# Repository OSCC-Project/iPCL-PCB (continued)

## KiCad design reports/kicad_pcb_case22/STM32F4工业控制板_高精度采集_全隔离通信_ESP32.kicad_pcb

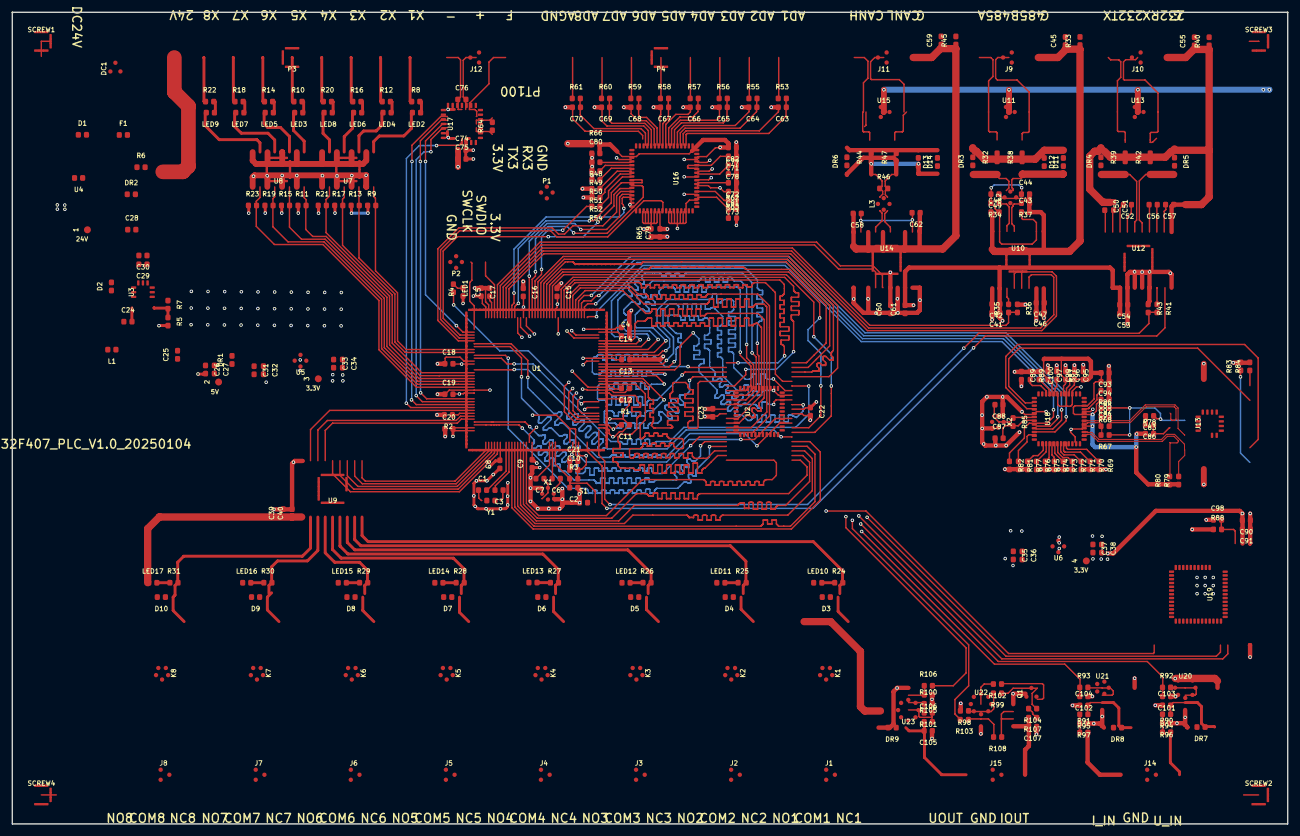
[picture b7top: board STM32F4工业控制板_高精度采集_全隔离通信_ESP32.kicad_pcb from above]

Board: 4 copper layers, 220.0 x 140.0 mm, 323 parts (0 on the bottom side), 298 nets.

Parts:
1: ie6183
2: ie6179
3: ie6175
4: ie6171
C1: ie6167
C2: ie6163
C3: ie6159
C4: ie6155
C5: ie6151
C6: ie6147
C7: ie6143
C8: ie6139
C9: ie6135
C10: ie6131
C11: ie6127
C12: ie6123
C13: ie6119
C14: ie6115
C15: ie6111
C16: ie6107
C17: ie6103
C18: ie6099
C19: ie6095
C20: ie6091
C21: ie6087
C22: ie6083
C23: ie6079
C24: ie6075
C25: ie6071
C26: ie6067
C27: ie6063
C28: ie6059
C29: ie6055
C30: ie6051
C31: ie6047
C32: ie6043
C33: ie6039
C34: ie6035
C35: ie6031
C36: ie6027
C37: ie6023
C38: ie6019
C39: ie6015
C40: ie6011
C41: ie6007
C42: ie6003
C43: ie5999
C44: ie5995
C45: ie5991
C46: ie5987
C47: ie5983
C48: ie5979
C49: ie5975
C50: ie5971
C51: ie5967
C52: ie5963
C53: ie5959
C54: ie5955
C55: ie5951
C56: ie5947
C57: ie5943
C58: ie5939
C59: ie5935
C60: ie5931
C61: ie5927
C62: ie5923
C63: ie5919
C64: ie5915
C65: ie5911
C66: ie5907
C67: ie5903
C68: ie5899
C69: ie5895
C70: ie5891
C71: ie5887
C72: ie5883
C73: ie5879
C74: ie5875
C75: ie5871
C76: ie5867
C77: ie5863
C78: ie5859
C79: ie5855
C80: ie5851
C81: ie5847
C82: ie5843
C83: ie5839
C84: ie5835
C85: ie5831
C86: ie5827
C87: ie5823
C88: ie5819
C89: ie5815
C90: ie5811
C91: ie5807
C92: ie5803
C93: ie5799
C94: ie5795
C95: ie5791
C96: ie5787
C97: ie5783
C98: ie5779
C99: ie5775
C100: ie5771
C101: ie5767
C102: ie5763
C103: ie5759
C104: ie5755
C105: ie5751
C106: ie5747
C107: ie5743
D1: ie5739
D2: ie5735
D3: ie5731
D4: ie5727
D5: ie5723
D6: ie5719
D7: ie5715
D8: ie5711
D9: ie5707
D10: ie5703
D11: ie5699
D12: ie5695
D13: ie5691
D14: ie5687
DC1: ie5683
DR1: ie5679
DR2: ie5675
DR3: ie5671
DR4: ie5667
DR5: ie5663
DR6: ie5659
DR7: ie5655
DR8: ie5651
DR9: ie5647
F1: ie5643
J1: ie5639
J2: ie5635
J3: ie5631
J4: ie5627
J5: ie5623
J6: ie5619
J7: ie5615
J8: ie5611
J9: ie5607
J10: ie5603
J11: ie5599
J12: ie5595
J13: ie4895
J14: ie5591
J15: ie5587
K1: ie5583
K2: ie5579
K3: ie5575
K4: ie5571
K5: ie5567
K6: ie5563
K7: ie5559
K8: ie5555
L1: ie5551
L2: ie5547
L3: ie5543
LED1: ie5539
LED2: ie5535
LED3: ie5531
LED4: ie5527
LED5: ie5523
LED6: ie5519
LED7: ie5515
LED8: ie5511
LED9: ie5507
LED10: ie5503
LED11: ie5499
LED12: ie5495
LED13: ie5491
LED14: ie5487
LED15: ie5483
LED16: ie5479
LED17: ie5475
P1: ie5471
P2: ie5467
P3: ie4915
P4: ie5463
Q1: ie5459
R1: ie5455
R2: ie5451
R3: ie5447
R4: ie5443
R5: ie5439
R6: ie5435
R7: ie5431
R8: ie5427
R9: ie5423
R10: ie5419
R11: ie5415
R12: ie5411
R13: ie5407
R14: ie5403
R15: ie5399
R16: ie5395
R17: ie5391
R18: ie5387
R19: ie5383
R20: ie5379
R21: ie5375
R22: ie5371
R23: ie5367
R24: ie5363
R25: ie5359
R26: ie5355
R27: ie5351
R28: ie5347
R29: ie5343
R30: ie5339
R31: ie5335
R32: ie5331
R33: ie5327
R34: ie5323
R35: ie5319
R36: ie5315
R37: ie5311
R38: ie5307
R39: ie5303
R40: ie5299
R41: ie5295
R42: ie5291
R43: ie5287
R44: ie5283
R45: ie5279
R46: ie5275
R47: ie5271
R48: ie5267
R49: ie5263
R50: ie5259
R51: ie5255
R52: ie5251
R53: ie5247
R54: ie5243
R55: ie5239
R56: ie5235
R57: ie5231
R58: ie5227
R59: ie5223
R60: ie5219
R61: ie5215
R62: ie5211
R63: ie5207
R64: ie5203
R65: ie5199
R66: ie5195
R67: ie5191
R68: ie5187
R69: ie5183
R70: ie5179
R71: ie5175
R72: ie5171
R73: ie5167
R74: ie5163
R75: ie5159
R76: ie5155
R77: ie5151
R78: ie5147
R79: ie5143
R80: ie5139
R81: ie5135
R82: ie5131
R83: ie5127
R84: ie5123
R85: ie5119
R86: ie5115
R87: ie5111
R88: ie5107
R89: ie5103
R90: ie5099
R91: ie5095
R92: ie5091
R93: ie5087
R94: ie5083
R95: ie5079
R96: ie5075
R97: ie5071
R98: ie5067
R99: ie5063
R100: ie5059
R101: ie5055
R102: ie5051
R103: ie5047
R104: ie5043
R105: ie5039
R106: ie5035
R107: ie5031
R108: ie5027
S1: ie5023
SCREW1: ie5019
SCREW2: ie5015
SCREW3: ie5011
SCREW4: ie4911
U1: ie4903
U2: ie4899
U3: ie5007
U4: ie5003
U5: ie4999
U6: ie4995
U7: ie4991
U8: ie4987
U9: ie4983
U10: ie4979
U11: ie4975
U12: ie4971
U13: ie4967
U14: ie4963
U15: ie4959
U16: ie4955
U17: ie4951
U18: ie4947
U19: ie4943
U20: ie4907
U21: ie4935
U22: ie4939
U23: ie4931
X1: ie4927
X2: ie4923
Y1: ie4919

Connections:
3.3V: 3.1, 4.1, C8.2, C9.2, C10.2, C11.2, C12.2, C13.2, C14.2, C15.2, C16.2, C17.2, C18.2, C19.2, C20.2, C21.2, C22.2, C23.2, C33.2, C34.2, C37.2, C38.2, C60.2, C74.2, C75.2, C79.2, C89.2, C90.2, C91.2, P1.1, P2.1, R3.2, R4.1, R9.1, R11.1, R13.1, R15.1, R17.1, R19.1, R21.1, R23.1, R51.2, R52.2, R63.2, R69.2, R70.2, R71.2, R77.2, R81.2, R82.2, R83.2, R84.2, R87.2, R88.1, U1.6, U1.17, U1.30, U1.32, U1.33, U1.39, U1.52, U1.62, U1.72, U1.84, U1.95, U1.108, U1.121, U1.131, U1.143, U1.144, U2.11, U2.33, U5.2, U5.4, U6.2, U6.4, U14.6, U16.23, U17.19, U17.20, U18.28, U19.2
3.3VA: C92.2, C93.2, C94.2, C95.2, C96.2, C97.2, R78.1, R79.1, R80.1, R87.1, U18.4, U18.8, U18.11, U18.15, U18.17, U18.21
5V: 2.1, C25.1, C26.2, C27.2, C31.2, C32.2, C35.2, C36.2, C41.1, C42.1, C46.2, C47.2, C53.2, C54.2, C61.2, DR1.1, L1.2, Q1.3, R5.2, R66.1, U5.3, U6.3, U10.2, U10.7, U12.2, U12.3, U14.8, U20.8, U21.8, U22.8
24V: 1.1, C28.1, C29.2, C30.2, C39.1, C40.1, D3.2, D4.2, D5.2, D6.2, D7.2, D8.2, D9.2, D10.2, DR2.1, F1.2, K1.1, K2.1, K3.1, K4.1, K5.1, K6.1, K7.1, K8.1, LED10.1, LED11.1, LED12.1, LED13.1, LED14.1, LED15.1, LED16.1, LED17.1, P3.9, R6.2, U3.7, U9.10, U23.8
232_GND: C50.1, C51.1, C55.1, C57.1, DR4.2, DR5.1, J10.1, R40.1, U12.11
232_RX: J10.2, R42.2, U13.3
232_TX: J10.3, R39.2, U13.1
485A: J9.3, R32.2, U11.1
485B: J9.2, R38.2, U11.3
485_GND: C43.2, C44.2, C45.1, C48.1, C49.1, J9.1, R33.1, R37.1, U10.9, U10.16
A5V: C80.2, C81.2, C82.2, R66.2, U16.1, U16.37, U16.38, U16.48
ACTLED: J13.10, U18.27
AD1: P4.1, R53.1
AD2: P4.2, R55.1
AD3: P4.3, R56.1
AD4: P4.4, R57.1
AD5: P4.5, R58.1
AD6: P4.6, R59.1
AD7: P4.7, R60.1
AD8: P4.8, R61.1
AD_BUSY: U1.93, U16.14
AD_CONVST: U1.98, U16.9, U16.10
AD_FASTDATA: U1.99, U16.15
AD_RANGE: R54.2, U1.91
AD_RESET: U1.92, U16.11
AD_SPI3_CS: U1.113, U16.13
AD_SPI3_MISO: U1.112, U16.24
AD_SPI3_SCLK: U1.111, U16.12
AGND: C63.2, C64.2, C65.2, C66.2, C67.2, C68.2, C69.2, C70.2, C71.1, C72.1, C73.1, C77.2, C78.1, C80.1, C81.1, C82.1, P4.9, R48.2, R49.2, R50.2, R62.2, R65.2, U16.2, U16.16, U16.17, U16.18, U16.19, U16.20, U16.21, U16.22, U16.26, U16.27, U16.28, U16.29, U16.30, U16.31, U16.32, U16.33, U16.35, U16.40, U16.41, U16.43, U16.46, U16.47, U16.50, U16.52, U16.54, U16.56, U16.58, U16.60, U16.62, U16.64
CANH: J11.3, R44.2, U15.1
CANL: J11.2, R47.2, U15.3
CAN_GND: C58.2, C59.1, C62.1, J11.1, R45.1, U14.11, U14.13, U14.16, U14.18, U14.20
COM1: J1.2, K1.2
COM2: J2.2, K2.2
COM3: J3.2, K3.2
COM4: J4.2, K4.2
COM5: J5.2, K5.2
COM6: J6.2, K6.2
COM7: J7.2, K7.2
COM8: J8.2, K8.2
DI_GND: U7.2, U7.4, U7.6, U7.8, U8.2, U8.4, U8.6, U8.8
EN: C98.2, R88.2, U19.3
ESP32_IO0: U1.45, U19.27
ESP32_RX6: U1.97, U19.37
ESP32_TX6: U1.96, U19.36
FORCE: J12.1, U17.5, U17.6
GND: C2.1, C4.2, C5.2, C8.1, C9.1, C10.1, C11.1, C12.1, C13.1, C14.1, C15.1, C16.1, C17.1, C18.1, C19.1, C20.1, C21.1, C22.1, C23.1, C25.2, C26.1, C27.1, C28.2, C29.1, C30.1, C31.1, C32.1, C33.1, C34.1, C35.1, C36.1, C37.1, C38.1, C39.2, C40.2, C41.2, C42.2, C46.1, C47.1, C53.1, C54.1, C60.1, C61.1, C74.1, C75.1, C79.1, C83.2, C86.2, C87.1, C88.1, C89.1, C90.1, C91.1, C92.1, C93.1, C94.1, C95.1, C96.1, C97.1, C98.1, C99.1, C100.1, C101.1, C102.1, C103.1, C104.1, C105.1, C106.1, C107.1, D2.1, DC1.2, DC1.3, DR1.2, DR2.2, DR7.2, DR8.2, DR9.2, J13.SH1, J13.SH2, J14.2, J15.2, P1.4, P2.4, R1.1, R2.2, R7.1, R36.1, R43.1, R65.1, R72.2, R73.2, R74.2, R75.2, R76.2, R86.1, R89.1, R96.1, R97.1, R98.2, R100.2, S1.1, U1.16, U1.31, U1.38, U1.51, U1.61, U1.83, U1.94, U1.107, U1.120, U1.130, U2.12, U2.34, U3.6, U3.9, U4.2, U5.1, U6.1, U7.9, U7.11, U7.13, U7.15, U8.9, U8.11, U8.13, U8.15, U9.9, U10.1, U10.8, U12.4, U12.5, U12.6, U12.7, U12.10, U14.1, U14.3, U14.7, U14.9, U14.10, U17.10, U17.15, U17.16, U17.21, U17.ie24, U17.ie25, U17.ie26, U17.ie27, U18.3, U18.9, U18.14, U18.16, U18.19, U18.29, U18.48, U19.1, U19.40, U19.41, U20.4, U21.4, U22.4, U23.4, X1.2, X1.4, X2.2, X2.4
I_IN2: J14.1, R91.2
I_OUT1: C107.2, J15.3, R107.2, U22.5
LINKLED: J13.11, U18.25
MCU_232_RX2: R41.2, R43.2, U1.37
MCU_232_TX2: U1.36, U12.9
MCU_485_DIR: U1.100, U10.4, U10.5
MCU_485_RX1: R35.1, R36.2, U1.102
MCU_485_TX1: U1.101, U10.6
MCU_ADC1: C101.2, R92.1, U1.42
MCU_ADC2: C102.2, R93.1, U1.43
MCU_CAN1_RX: U1.103, U14.4
MCU_CAN1_TX: U1.104, U14.5
MCU_DAC1: R103.2, U1.40
MCU_DAC2: R106.2, U1.41
MCU_DI1: R9.2, U1.116, U7.16
MCU_DI2: R13.2, U1.117, U7.14
MCU_DI3: R17.2, U1.124, U7.12
MCU_DI4: R21.2, U1.125, U7.10
MCU_DI5: R11.2, U1.126, U8.16
MCU_DI6: R15.2, U1.127, U8.14
MCU_DI7: R19.2, U1.128, U8.12
MCU_DI8: R23.2, U1.129, U8.10
MCU_OUT1: U1.1, U9.1
MCU_OUT2: U1.2, U9.2
MCU_OUT3: U1.3, U9.3
MCU_OUT4: U1.4, U9.4
MCU_OUT5: U1.5, U9.5
MCU_OUT6: U1.140, U9.6
MCU_OUT7: U1.139, U9.7
MCU_OUT8: U1.137, U9.8
NC1: J1.3, K1.4
NC2: J2.3, K2.4
NC3: J3.3, K3.4
NC4: J4.3, K4.4
NC5: J5.3, K5.4
NC6: J6.3, K6.4
NC7: J7.3, K7.4
NC8: J8.3, K8.4
NETC1_1: C1.1, Y1.2
NETC3_1: C3.1, Y1.1
NETC4_1: C4.1, U1.71
NETC5_1: C5.1, U1.106
NETC6_1: C6.1, X1.3
NETC7_1: C7.1, X1.1
NETC24_1: C24.1, D2.2, L1.1, U3.8
NETC24_2: C24.2, U3.1
NETC43_1: C43.1, C44.1, C48.2, C49.2, R34.2, U10.10, U10.15
NETC50_2: C50.2, U12.20
NETC51_2: C51.2, U12.19
NETC52_1: C52.1, U12.17
NETC52_2: C52.2, U12.18
NETC56_1: C56.1, U12.13
NETC56_2: C56.2, U12.14
NETC57_2: C57.2, U12.12
NETC58_1: C58.1, C62.2, U14.12, U14.19
NETC71_2: C71.2, U16.44, U16.45
NETC72_2: C72.2, U16.39
NETC73_2: C73.2, U16.36
NETC84_2: C84.2, J13.6
NETC85_2: C85.2, J13.3
NETC87_2: C87.2, R85.2, U18.31, X2.3
NETC88_2: C88.2, R85.1, U18.30, X2.1
NETC99_2: C99.2, U18.20
NETC100_2: C100.2, U18.22
NETC103_2: C103.2, DR7.1, R94.1, U20.3
NETC104_2: C104.2, DR8.1, R95.1, U21.3
NETC106_2: C106.2, R106.1, U23.3
NETD1_1: D1.1, DC1.1
NETD1_2: D1.2, F1.1
NETD11_1: D11.1, D12.2, DR3.2
NETD11_2: D11.2, D12.1, L2.3, R38.1
NETD13_1: D13.1, D14.2, L3.4, R44.1, R46.1
NETD13_2: D13.2, D14.1, DR6.2
NETDR3_1: DR3.1, L2.4, R32.1
NETDR4_1: DR4.1, R39.1, U12.16
NETDR5_2: DR5.2, R42.1, U12.15
NETDR6_1: DR6.1, L3.3, R46.2, R47.1
NETJ13_9: J13.9, R83.1
NETJ13_12: J13.12, R84.1
NETL2_1: L2.1, R34.1, U10.14
NETL2_2: L2.2, R37.2, U10.13
NETL3_1: L3.1, U14.17
NETL3_2: L3.2, U14.15
NETLED1_1: LED1.1, R4.2
NETLED2_1: LED2.1, R8.2
NETLED2_2: LED2.2, U7.1
NETLED3_1: LED3.1, R10.2
NETLED3_2: LED3.2, U8.1
NETLED4_1: LED4.1, R12.2
NETLED4_2: LED4.2, U7.3
NETLED5_1: LED5.1, R14.2
NETLED5_2: LED5.2, U8.3
NETLED6_1: LED6.1, R16.2
NETLED6_2: LED6.2, U7.5
NETLED7_1: LED7.1, R18.2
NETLED7_2: LED7.2, U8.5
NETLED8_1: LED8.1, R20.2
NETLED8_2: LED8.2, U7.7
NETLED9_1: LED9.1, R22.2
NETLED9_2: LED9.2, U8.7
NETLED10_2: LED10.2, R24.1
NETLED11_2: LED11.2, R25.1
NETLED12_2: LED12.2, R26.1
NETLED13_2: LED13.2, R27.1
NETLED14_2: LED14.2, R28.1
NETLED15_2: LED15.2, R29.1
NETLED16_2: LED16.2, R30.1
NETLED17_2: LED17.2, R31.1
NETQ1_1: Q1.1, R102.1
NETQ1_2: Q1.2, R99.1, R104.1
NETR1_2: R1.2, U1.48
NETR2_1: R2.1, U1.138
NETR5_1: R5.1, R7.2, U3.4
NETR6_1: R6.1, U4.1
NETR35_2: R35.2, U10.3
NETR41_1: R41.1, U12.8
NETR48_1: R48.1, U16.3
NETR49_1: R49.1, U16.4
NETR50_1: R50.1, U16.5
NETR51_1: R51.1, U16.6
NETR52_1: R52.1, U16.7
NETR54_1: R54.1, U16.8
NETR62_1: R62.1, R63.1, U16.34
NETR64_1: R64.1, U17.1, U17.2
NETR64_2: R64.2, U17.3, U17.4
NETR69_1: R69.1, U18.45
NETR70_1: R70.1, U18.44
NETR71_1: R71.1, U18.43
NETR72_1: R72.1, U18.42
NETR73_1: R73.1, U18.41
NETR74_1: R74.1, U18.40
NETR75_1: R75.1, U18.39
NETR76_1: R76.1, U18.38
NETR77_1: R77.1, U18.37
NETR81_1: R81.1, U18.36
NETR86_2: R86.2, U18.10
NETR89_2: R89.2, U18.23
NETR90_1: R90.1, R94.2, R96.2
NETR91_1: R91.1, R95.2, R97.2
NETR92_2: R92.2, U20.1, U20.2
NETR93_2: R93.2, U21.1, U21.2
NETR98_1: R98.1, R99.2, U22.2
NETR100_1: R100.1, R101.2, U23.2
NETR101_1: R101.1, R105.2, U23.1
NETR102_2: R102.2, U22.1
NETR103_1: R103.1, R108.2, U22.3
NETR104_2: R104.2, R107.1
NETR108_1: R108.1, U22.6, U22.7
NO1: J1.1, K1.3
NO2: J2.1, K2.3
NO3: J3.1, K3.3
NO4: J4.1, K4.3
NO5: J5.1, K5.3
NO6: J6.1, K6.3
NO7: J7.1, K7.3
NO8: J8.1, K8.3
NRST: C2.2, R3.1, S1.2, U1.25
OSC32_IN: C1.2, U1.8
OSC32_OUT: C3.2, U1.9
OSC_IN: C7.2, U1.23
OSC_OUT: C6.2, U1.24
OUT1: D3.1, K1.5, R24.2, U9.18
OUT2: D4.1, K2.5, R25.2, U9.17
OUT3: D5.1, K3.5, R26.2, U9.16
OUT4: D6.1, K4.5, R27.2, U9.15
OUT5: D7.1, K5.5, R28.2, U9.14
OUT6: D8.1, K6.5, R29.2, U9.13
OUT7: D9.1, K7.5, R30.2, U9.12
OUT8: D10.1, K8.5, R31.2, U9.11
PGND: C45.2, C55.2, C59.2, R33.2, R40.2, R45.2, SCREW1.1, SCREW2.1, SCREW3.1, SCREW4.1, U11.2, U13.2, U15.2
PT_DRDY: U1.136, U17.18
PT_SPI1_CS: U1.110, U17.13
PT_SPI1_MISO: U1.134, U17.14
PT_SPI1_MOSI: U1.135, U17.11
PT_SPI1_SCLK: U1.133, U17.12
RCT: C83.1, J13.5, R67.1, R68.1
RTD+: C76.2, J12.2, U17.7
RTD-: C76.1, J12.3, U17.8, U17.9
RUN: LED1.2, U1.47
RX3: P1.3, U1.70
RXN: C84.1, R67.2, U18.5
RXP: C85.1, R68.2, U18.6
SRAM_A0: U1.10, U2.5
SRAM_A1: U1.11, U2.4
SRAM_A2: U1.12, U2.3
SRAM_A3: U1.13, U2.2
SRAM_A4: U1.14, U2.1
SRAM_A5: U1.15, U2.44
SRAM_A6: U1.50, U2.43
SRAM_A7: U1.53, U2.42
SRAM_A8: U1.54, U2.27
SRAM_A9: U1.55, U2.26
SRAM_A10: U1.56, U2.25
SRAM_A11: U1.57, U2.24
SRAM_A12: U1.87, U2.22
SRAM_A13: U1.88, U2.21
SRAM_A14: U1.89, U2.20
SRAM_A15: U1.90, U2.19
SRAM_A16: U1.80, U2.18
SRAM_A17: U1.81, U2.23
SRAM_A18: U1.82, U2.28
SRAM_CS1: U1.123, U2.6
SRAM_D0: U1.85, U2.7
SRAM_D1: U1.86, U2.8
SRAM_D2: U1.114, U2.9
SRAM_D3: U1.115, U2.10
SRAM_D4: U1.58, U2.13
SRAM_D5: U1.59, U2.14
SRAM_D6: U1.60, U2.15
SRAM_D7: U1.63, U2.16
SRAM_D8: U1.64, U2.29
SRAM_D9: U1.65, U2.30
SRAM_D10: U1.66, U2.31
SRAM_D11: U1.67, U2.32
SRAM_D12: U1.68, U2.35
SRAM_D13: U1.77, U2.36
SRAM_D14: U1.78, U2.37
SRAM_D15: U1.79, U2.38
SRAM_LB: U1.141, U2.39
SRAM_OE: U1.118, U2.41
SRAM_UB: U1.142, U2.40
SRAM_WE: U1.119, U2.17
SWCLK: P2.3, U1.109
SWDIO: P2.2, U1.105
TCT: C86.1, J13.4, R78.2
TX3: P1.2, U1.69
TXN: J13.2, R80.2, U18.1
TXP: J13.1, R79.2, U18.2
U_IN1: J14.3, R90.2
U_OUT2: C105.2, DR9.1, J15.1, R105.1
V1: C63.1, R53.2, U16.49
V2: C64.1, R55.2, U16.51
V3: C65.1, R56.2, U16.53
V4: C66.1, R57.2, U16.55
V5: C67.1, R58.2, U16.57
V6: C68.1, R59.2, U16.59
V7: C69.1, R60.2, U16.61
V8: C70.1, R61.2, U16.63
VREF2.5V: C77.1, C78.2, U16.42
W5500_SPI2_CS: R82.1, U1.73, U18.32
W5500_SPI2_MISO: U1.75, U18.34
W5500_SPI2_MOSI: U1.76, U18.35
W5500_SPI2_SCLK: U1.74, U18.33
X1: P3.1, R8.1
X2: P3.2, R12.1
X3: P3.3, R16.1
X4: P3.4, R20.1
X5: P3.5, R10.1
X6: P3.6, R14.1
X7: P3.7, R18.1
X8: P3.8, R22.1
